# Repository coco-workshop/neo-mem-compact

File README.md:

# neo-mem-compact

> ⚠️ **UNTESTED DESIGN.** None of these boards has been built or tried in a CoCo 3.
> They have only been checked on paper: design-rule checks, an independent pin-by-pin
> check against datasheets, and simulation of the DAT board's logic. Real hardware may
> still show timing or fit problems these checks can't catch. Build them at your own
> risk, order the smallest quantity you can, and treat a first batch as prototypes.

Compact surface-mount RAM expansions for the Tandy Color Computer 3. They plug into
the CN4/CN5/CN6 expansion sockets (and, for 2 MB, the CPU socket).

| Board | What it does | Main parts |
|---|---|---|
| [**512K memory**](boards/512k) | 512K upgrade on its own | CY62146ESL 256K×16 SRAM, 74AHCT86, 2× 74x574 |
| [**2048K memory**](boards/2048k-mem) | 2 MB of RAM; runs as 512K on its own | CY62167ELL 1M×16 SRAM, 74AHCT86, 2× 74x574 |
| [**DAT**](boards/dat) | Sits under the CPU and supplies the extra address bits the 2048K memory board needs; also drives an optional turbo LED | ATF1504AS CPLD |

**Which to build:**
* **512K:** the 512K memory board. It's the cheapest option.
* **2 MB:** the 2048K memory board plus the DAT board, joined by a short bank cable
  (both headers are 2×2, laid out like the GIME-Z's bank header).
  The memory board also runs alone as 512K, so you can fit it first and add the DAT
  board later.

| 512K memory | 2048K memory | DAT |
|---|---|---|
|  |  |  |
| [layout](boards/512k/docs/preview.png) | [layout](boards/2048k-mem/docs/preview.png) | [layout](boards/dat/docs/preview.png) · [with CPU fitted](boards/dat/docs/render-cpu.png) |

*3D renders of the assembled boards, made from the real PCB layers and KiCad's
standard part models (the DAT board's wire-wrap socket is drawn as a normal socket).
The "layout" links show the flat top and bottom views.*

**Status: untested - no board has been built yet.** What *has* been checked: all
three boards pass DRC, and each finished PCB was checked independently against
datasheet pinouts (`boards/*/docs/`). The DAT board's CPLD logic passes a cycle-level
simulation in both CPU speed modes, both as written and after fitting into the chip.
Not yet confirmed on real hardware: memory timing on a real GIME (and on faster GIME
replacements), the DAT board's bank timing against /RAS, and physical fit in the case.
The DAT board's outline was fitted to an Athena-style board's layout and measured
parts heights (see [Fitting](#fitting)), not to a real machine.

## Connectors, jumpers and features

### 512K memory board
| Ref | What | Use |
|---|---|---|
| J1 | 24-pin header, **underneath** | Plugs into CN6/CN5 (the vertical socket pair left of the RAM). Pin 1 (square pad) faces the rear ports. |
| J2 | 12-pin header, **underneath** | Plugs into CN4 (the horizontal socket above the keyboard connector). Pin 1 at the left end. |

No jumpers or settings.

### 2048K memory board
| Ref | What | Use |
|---|---|---|
| J1, J2 | Same as the 512K memory board | Same fitting. |
| J3 | 2×2 header on top: a **B** row and a **G** row | Bank input from the DAT board (or any source with the same layout as the GIME-Z bank header). Pin 1 is the square pad, a B pin. |

* **J3 left open:** runs as 512K (R1/R2 hold the bank lines low).
* **2×2 cable (pin 1 to pin 1):** B to B, G to G. The two B wires can go either way
  round; swapping them only reorders memory.
* **Two single leads:** only the two B pins are needed; the motherboard provides the ground.

### DAT board
| Ref | What | Use |
|---|---|---|
| J1 | 40-pin wire-wrap socket | Sits in the CPU socket, and the 6809/6309 plugs into it. Pin 1 is the square pad, marked "CPU pin 1". |
| J2 | 2×2 header: a **B** column (board edge) and a **G** column | Bank output to memory J3. Pin 1 is the square pad, a B pin. Both B lines have 100 Ω protection (R1/R2), so a plug turned round does no harm. |
| J3 | 2×5 JTAG header | Programs the CPLD with `dat2m_top.jed`. Atmel ATDH1150USB / USB-Blaster layout (1 TCK, 2 GND, 3 TDO, 4 +5V, 5 TMS, 9 TDI, 10 GND). The CoCo must be powered on while programming. |
| J4 | 1×2 turbo LED header | Pin 1 "+" (+5V) to the LED's anode, pin 2 to its cathode. The 470 Ω resistor (R3) is on the board, so connect the LED directly. |
| JP1 | 3-pad solder jumper, **on the back** | Mode select, marked "512K JP1 2MB". |

* **JP1 as made (pads 1–2 bridged):** 2MB mode. **To force 512K:** cut the 1–2 bridge
  and bridge 2–3. Use this for old programs that write junk into the MMU registers'
  top bits.
* **Turbo LED:** lights while the CPU runs fast (`POKE 65497,0`, i.e. any write to
  `$FFD9`). It goes off with `POKE 65496,0` (`$FFD8`) or a reset.
* **Using 2MB:** after reset the machine is a normal 512K CoCo 3. Software reaches the
  extra memory by writing bits 7:6 of the MMU registers (`$FFA0`–`$FFAF`); video
  memory uses `$FF9B` bits 1:0. NitrOS-9 configured for 2MB, or a 2MB memory test,
  does this for you.

## Repository layout
| Path | Contents |
|---|---|
| `boards/<board>/hardware` | KiCad 7 project (opens in KiCad 7, 8 and 9) |
| `boards/<board>/fab` | Gerbers + drill (zip), JLCPCB BOM and placement (CPL) files |
| `boards/<board>/docs` | Schematic PDF, 3D renders, flat layout preview, DRC and verification reports (plus the DAT board's bus pin check) |
| `docs/diagrams` | The diagrams used in this README (SVG) |
| `boards/dat/cpld` | CPLD logic, testbench, fitted `dat2m_top.jed`, build script |
| `scripts/512k`, `scripts/mem`, `scripts/dat` | Each board's design definition, generators and independent checker |
| `scripts/common` | Routing, clean-up, fab-output and rendering tools shared by all boards |

## How the memory boards work
Both memory boards replace the CoCo 3's four DRAMs with one 16-bit SRAM.

* The GIME multiplexes row and column addresses onto the same pins. Two '574
  flip-flops (U3/U4) latch the row address on the falling edge of /RAS, clocked
  through one XOR gate (`RAS = ~RAS XOR 1`). That gate delay centres the sampling
  point on the row-address hold time. On the 2048K memory board the same flip-flops also
  latch the two bank bits from the DAT board.
* Flip-flops are used rather than transparent latches ('573), so the row address
  holds after /RAS rises and can't change mid-cycle even if /CAS outlasts /RAS.
* `~BHE = ~WE0 XOR 1`, `~BLE = ~WE1 XOR 1`, `~WE = ~WE1 XOR ~BHE`
  (Jim Brain's simplification). If both write lines are ever low at once (an
  invalid state), the result is "no write".
* SRAM `~CE` = `/CAS`, `~OE` = GND. The chip only responds while the column address
  is valid, so glitches on the address lines or write logic before /CAS falls are
  ignored, and page-mode accesses are safe.
* SRAM address pins, and the data pins within each byte lane, are permuted to
  simplify routing. Any consistent one-to-one mapping works.
* The 2048K memory board's R1/R2 pull the bank bits low, so with no DAT board connected it
  runs as 512K.

## How the DAT board works (2 MB)
The GIME's MMU registers are only 6 bits wide, so it can only address 512K
(64 × 8K blocks). Every CoCo 3 2 MB upgrade, from the original Disto kit onward, adds a board on the CPU bus that keeps the missing top two bits
of each MMU register and supplies them as physical address lines A20:A19.

The CPLD only listens to the CPU bus. The only signals it drives are the two bank lines
and the turbo LED.

| Register | Kept by the DAT board |
|---|---|
| `$FFA0–$FFAF` | bits 7:6 of all 16 MMU registers (the GIME keeps bits 5:0) |
| `$FF90` | bit 6 (MMU enable), bit 3 (MC3, the constant `$FExx` page) |
| `$FF91` | bit 0 (task select) |
| `$FF9B` | bits 1:0, the video bank (the Disto convention, as used by NitrOS-9) |
| `$FFD8/$FFD9` | CPU speed, used to find the CPU slot |

For each GIME memory slot it outputs either the CPU bank or the video bank:
* **CPU slots:** `mmu[task, A15:A13]` bits 7:6. It outputs bank 0 when the MMU is
  off, and for `$FExx` when MC3 is set (matching the GIME).
* **Video slots:** `$FF9B` bits 1:0.

The GIME runs memory slots at a fixed ~3.58 MHz. Counting from E's falling edge, the
fast-mode pattern is video, CPU, and the slow-mode pattern is video, idle, video,
CPU. So the CPU slot is always the one that ends when E falls: "E high" in fast
mode, "E high and Q low" in slow mode. (This matches Tony Distefano's description of
the Disto 2-Meg kit.)

All of these registers are write-only (reads come from the GIME as usual) and are
cleared by /RESET, so a reset machine is a plain 512K CoCo 3 until software writes
bits 7:6.

**Turbo LED:** J4 (+5V, cathode through R3) drives a case LED that lights whenever
the CPU runs fast: any write to `$FFD9` turns it on; `$FFD8` or /RESET turns it off.

**512K mode:** solder jumper **JP1** on the back of the DAT board selects the mode.
It ships bridged 1–2 (2 MB). Re-bridge it 2–3 to force bank 0, for any old program
that writes junk into bits 7:6 of the MMU registers.

The DAT board doesn't buffer or protect the CPU bus. It only listens: every CPLD pin
on the CPU bus is an input, the four clock and control lines (E, Q, R/W, /RESET) use
input-only pins that can't drive at all, and the bus safety check (see
[The CPLD](#the-cpld-boardsdatcpld)) rejects any build that would make a bus pin an
output. Its two bank outputs pass through 100 Ω resistors (R1/R2), so a cable plugged
in backwards can't short them.

## Fitting
1. **Memory board (either size):** remove the four DRAMs (IC16–IC19) and cut C65 and
   C66. On a PAL machine they're left of the GIME; on an NTSC machine they're nearer
   the DRAM sockets. J1 goes into CN6/CN5 (the vertical socket pair left of the
   DRAM), with pin 1 (square pad) toward the rear ports. J2 goes into CN4 (the
   horizontal socket above the keyboard connector), with pin 1 at the left end.
2. **DAT board (2 MB only):** the CPU must be socketed. Pull the 6809/6309, plug the
   DAT board into the CPU socket with pin 1 (square pad, marked "CPU pin 1")
   matching the socket's pin 1, then plug the CPU into the DAT board. The board is
   30.1 × 65.5 mm and sits about 5 mm up, on top of the CPU socket:
   * Over the socket it is the CPU's width, with a slim tab (8.5 mm wide) on the
     pin-1 side holding the turbo LED (J4), bank (J2) and JTAG (J3) headers. The tab
     starts about halfway along the socket, clear of the tall caps near the pin-1
     end (C2, C56).
   * The CPLD end reaches 16 mm past the CPU's pin-20 end and is 3.8 mm wider on
     the pin-21 side. On the Athena layout it stays clear of the parts around it:
     about 3.7 mm to C4, 7.2 mm to a OneROM in the ROM socket, 7.9 mm to C55.
   * Anything under the board taller than the socket (5 mm) must be moved or laid
     flat, for example a capacitor added just past the CPU's pin-20 end.
3. Link DAT **J2** to memory **J3** with a short 2×2 female–female cable wired pin 1
   to pin 1. Both headers have a **B** pair and a **G** pair (marked on the
   silkscreen; pin 1 = square pad = B): match B to B and G to G. Which B goes to
   which doesn't matter - swapping the two bank lines only reorders memory. Two
   single leads on the B pins alone also work (the grounds are extra). See the
   [bank cable diagram](docs/diagrams/bank-cable.svg).

## The CPLD (`boards/dat/cpld`)
* `dat2m.v` holds the logic and `dat2m_tb.v` is its testbench
  (`iverilog dat2m.v dat2m_tb.v && vvp a.out`).
* `dat2m_top.v` is the top level. It's generated from the PCB, so its `//PIN:` list
  matches the copper exactly.
* **`dat2m_top.jed` is ready to program** (`dat2m_top.fit` is the fitter report).
  It was built with [hoglet67/atf15xx_yosys](https://github.com/hoglet67/atf15xx_yosys)
  (Yosys plus Atmel's `fit1504` from ProChip 5.0.x, run under Wine). With every pin
  locked to the PCB it fits in 50 of 64 macrocells, with E on the global clock
  (pin 37), /RESET on global clear (pin 39) and the turbo LED on pin 14. The
  fitter's gate-level output passes the same 129-check testbench as the source.
* To rebuild: `ATF15XX=/path/to/atf15xx_yosys boards/dat/cpld/build.sh`. It
  synthesises, fits, and re-runs the testbench on the fitted netlist.
* **Bus safety check:** `scripts/dat/check_pins.py` reads the fitter report
  (`dat2m_top.fit`) and the PCB and fails unless BANK0, BANK1 and the turbo LED are the only outputs,
  every CPLD pin wired to the CPU socket is an input, and the pins the fitter
  left unused are unconnected. `build.sh` runs it after every fit; the result for
  the committed `.jed` is in `boards/dat/docs/pin-check.txt`.
* In `dat2m_top.v` the E and Q inputs are called `ECLK`/`QCLK`: top-level ports named
  `E` or `Q` clash with cell pin names, and `fit1504` then rejects the netlist.
* Program `dat2m_top.jed` through J3 (10-pin, Atmel ATDH1150USB / USB-Blaster layout)
  with Microchip ATMISP (included with ProChip). Or convert it to SVF and play it
  with OpenOCD or UrJTAG from any compatible adapter. Power the CoCo while
  programming.

## Ordering (JLCPCB)
**These are untested prototypes** (see the warning at the top): order the minimum
quantity, and expect that a first build may need fixes.

Each board has its own Gerbers, BOM and CPL file in `boards/<board>/fab/`. Upload the
gerbers zip (2 layers, 1.6 mm), then the BOM and CPL for assembly. Check part
rotations in JLC's placement preview: each chip's pin-1 dot should sit on its
silkscreen triangle. Ordering all boards together shares shipping.

**Parts (both memory boards):**
| Ref | Part | LCSC | Alternatives |
|---|---|---|---|
| U2 | TI SN74AHCT86PWR | C471866 | Nexperia 74AHCT86PW (C554719), or any 5 V TTL-input '86 in TSSOP-14 (AHCT, VHCT, ACT). Not HCT: too slow for the /RAS clock path. |
| U3, U4 | Toshiba 74VHCT574AFT(BE) | C7421311 | Nexperia 74AHCT574PW (C282328), Toshiba 74VHCT574AFT (C2677834), any ACT574 in TSSOP-20; HCT574 as a last resort (slower, less margin) |
| U1 (512K) | CY62146ESL-45ZSXIT (reel) | C2953196 | CY62146ESL-45ZSXI (the same chip on a tray, e.g. from DigiKey or Mouser), or the dearer CY62146ELL. Not the CY62146EV30 (3 V only). |
| U1 (2048K) | CY62167ELL-45ZXI | C2950509 | Not the CY62167EV30 (3 V only). |

**Never** use HC (CMOS-level inputs), LV or LVC (3.3 V) logic.

**DAT board:**
* **U1:** ATF1504AS-10AU44. LCSC (C219301) is usually out of stock and expensive;
  DigiKey, Mouser and RS stock it for about $5. Untick U1 in JLC's BOM, let JLC fit
  the 0402 capacitors and resistors, and hand-solder the CPLD (TQFP-44, 0.8 mm pitch).
* **R1, R2** 100 Ω (C25076) and **R3** 470 Ω (C25117), all JLC basic parts.
* **J1** is a 40-pin **wire-wrap** DIP socket (long square tails, e.g. Mill-Max
  123-43-640-41-001000), mounted on top with its tails pushed through the board and
  trimmed to about 6 mm, so they plug into the CoCo's CPU socket. The holes are
  1.0 mm for the 0.64 mm square tails.

**Hand-solder** all through-hole parts: memory board headers J1/J2 on the
**bottom** (J3, 2×2, on top, 2048K memory board only), and the DAT board's J1, J2 (2×2),
J3 (2×5, JTAG) and J4 (1×2, turbo LED).

## First power-up
1. Check for shorts between +5V and GND on every board.
2. Fit the memory board alone and run a full 512K memory test (e.g. under NitrOS-9,
   or a RAM test program). On the 2048K memory board leave J3 open (bank 0).
3. If you have a scope, check /WE0 and /WE1 against /CAS at the end of a write. The
   design assumes /CAS rises before, or together with, the write line.
4. **2 MB:** program the CPLD, fit the DAT board, and check the machine boots as a
   512K CoCo 3. Then check BANK0/BANK1 at memory J3 settle **before** /RAS falls (it's
   latched there), in both fast and slow mode. The design expects /RAS to fall at
   least ~15 ns after the E/Q edge that starts the slot. Probe E and Q on the CPU's
   own pins, the bank lines on the DAT board's J2 B pins, and GND/+5V on its JTAG header.
5. Test 2 MB with NitrOS-9 configured for 2 MB, or a 2 MB memory test.

## Regenerating
Each board is defined in `scripts/<board>/design.py` (`512k`, `mem`, `dat`). Needs
KiCad 7's Python bindings (`pcbnew`), `shapely`, `scipy`, Java 21 and
[Freerouting](https://github.com/freerouting/freerouting) 2.x. For example, the
2048K memory board:
```sh
B=boards/2048k-mem/hardware/neo-mem-2048k-mem
python3 scripts/mem/make_sch.py && python3 scripts/mem/make_pcb.py      # unrouted board
FREEROUTING_JAR=/path/freerouting-2.1.0.jar FR_EXTRA=--router.optimizer.max_passes=40 \
  python3 scripts/common/route.py $B.kicad_pcb /tmp/r.kicad_pcb 60
python3 scripts/common/finish.py /tmp/r.kicad_pcb /tmp/drc.txt          # strip stubs, DRC
python3 scripts/common/schnets.py /tmp/r.kicad_pcb $B.kicad_pro
cp /tmp/r.kicad_pcb $B.kicad_pcb
python3 scripts/mem/verify.py $B.kicad_pcb $B.kicad_sch
python3 scripts/common/fab.py boards/2048k-mem/hardware neo-mem-2048k-mem \
  boards/2048k-mem/fab boards/2048k-mem/docs scripts/mem/bom.json
```
The 512K memory and DAT boards work the same way (the DAT checker also takes
`boards/dat/cpld/dat2m_top.v`, and `finish.py` takes `JP1` as a keepout). The memory
boards' fine pitches need the 0.15 mm default clearance set in their `.kicad_pro`
(the DAT board uses 0.2 mm). Autorouting
isn't deterministic; the committed boards are the ones that were checked.

The 3D renders (`boards/*/docs/render*.png`) come from
`python3 scripts/common/render_all.py`, which also needs `rsvg-convert`, `pyvista`
and `cadquery-ocp`. It downloads KiCad's STEP part models into `~/.cache/kicad-3d`
the first time. The diagrams in `docs/diagrams` are hand-drawn SVGs, except
`dat-timing.svg`, which `python3 scripts/common/diagram_timing.py` generates.

## License and credit
Derived from **cc3-512k** by Ciaran Anscomb (<https://gitlab.com/sixxie/cc3-512k>):
the traced CN4/CN5/CN6 pinout, connector positions, outline envelope and design
approach, with the XOR logic from Jim Brain (RETRO Innovations). The DAT approach
follows Tony Distefano's published description of the Disto 2-Meg kit. Released,
like the original, under the
[Creative Commons Attribution-ShareAlike 4.0 International](LICENSE) license.

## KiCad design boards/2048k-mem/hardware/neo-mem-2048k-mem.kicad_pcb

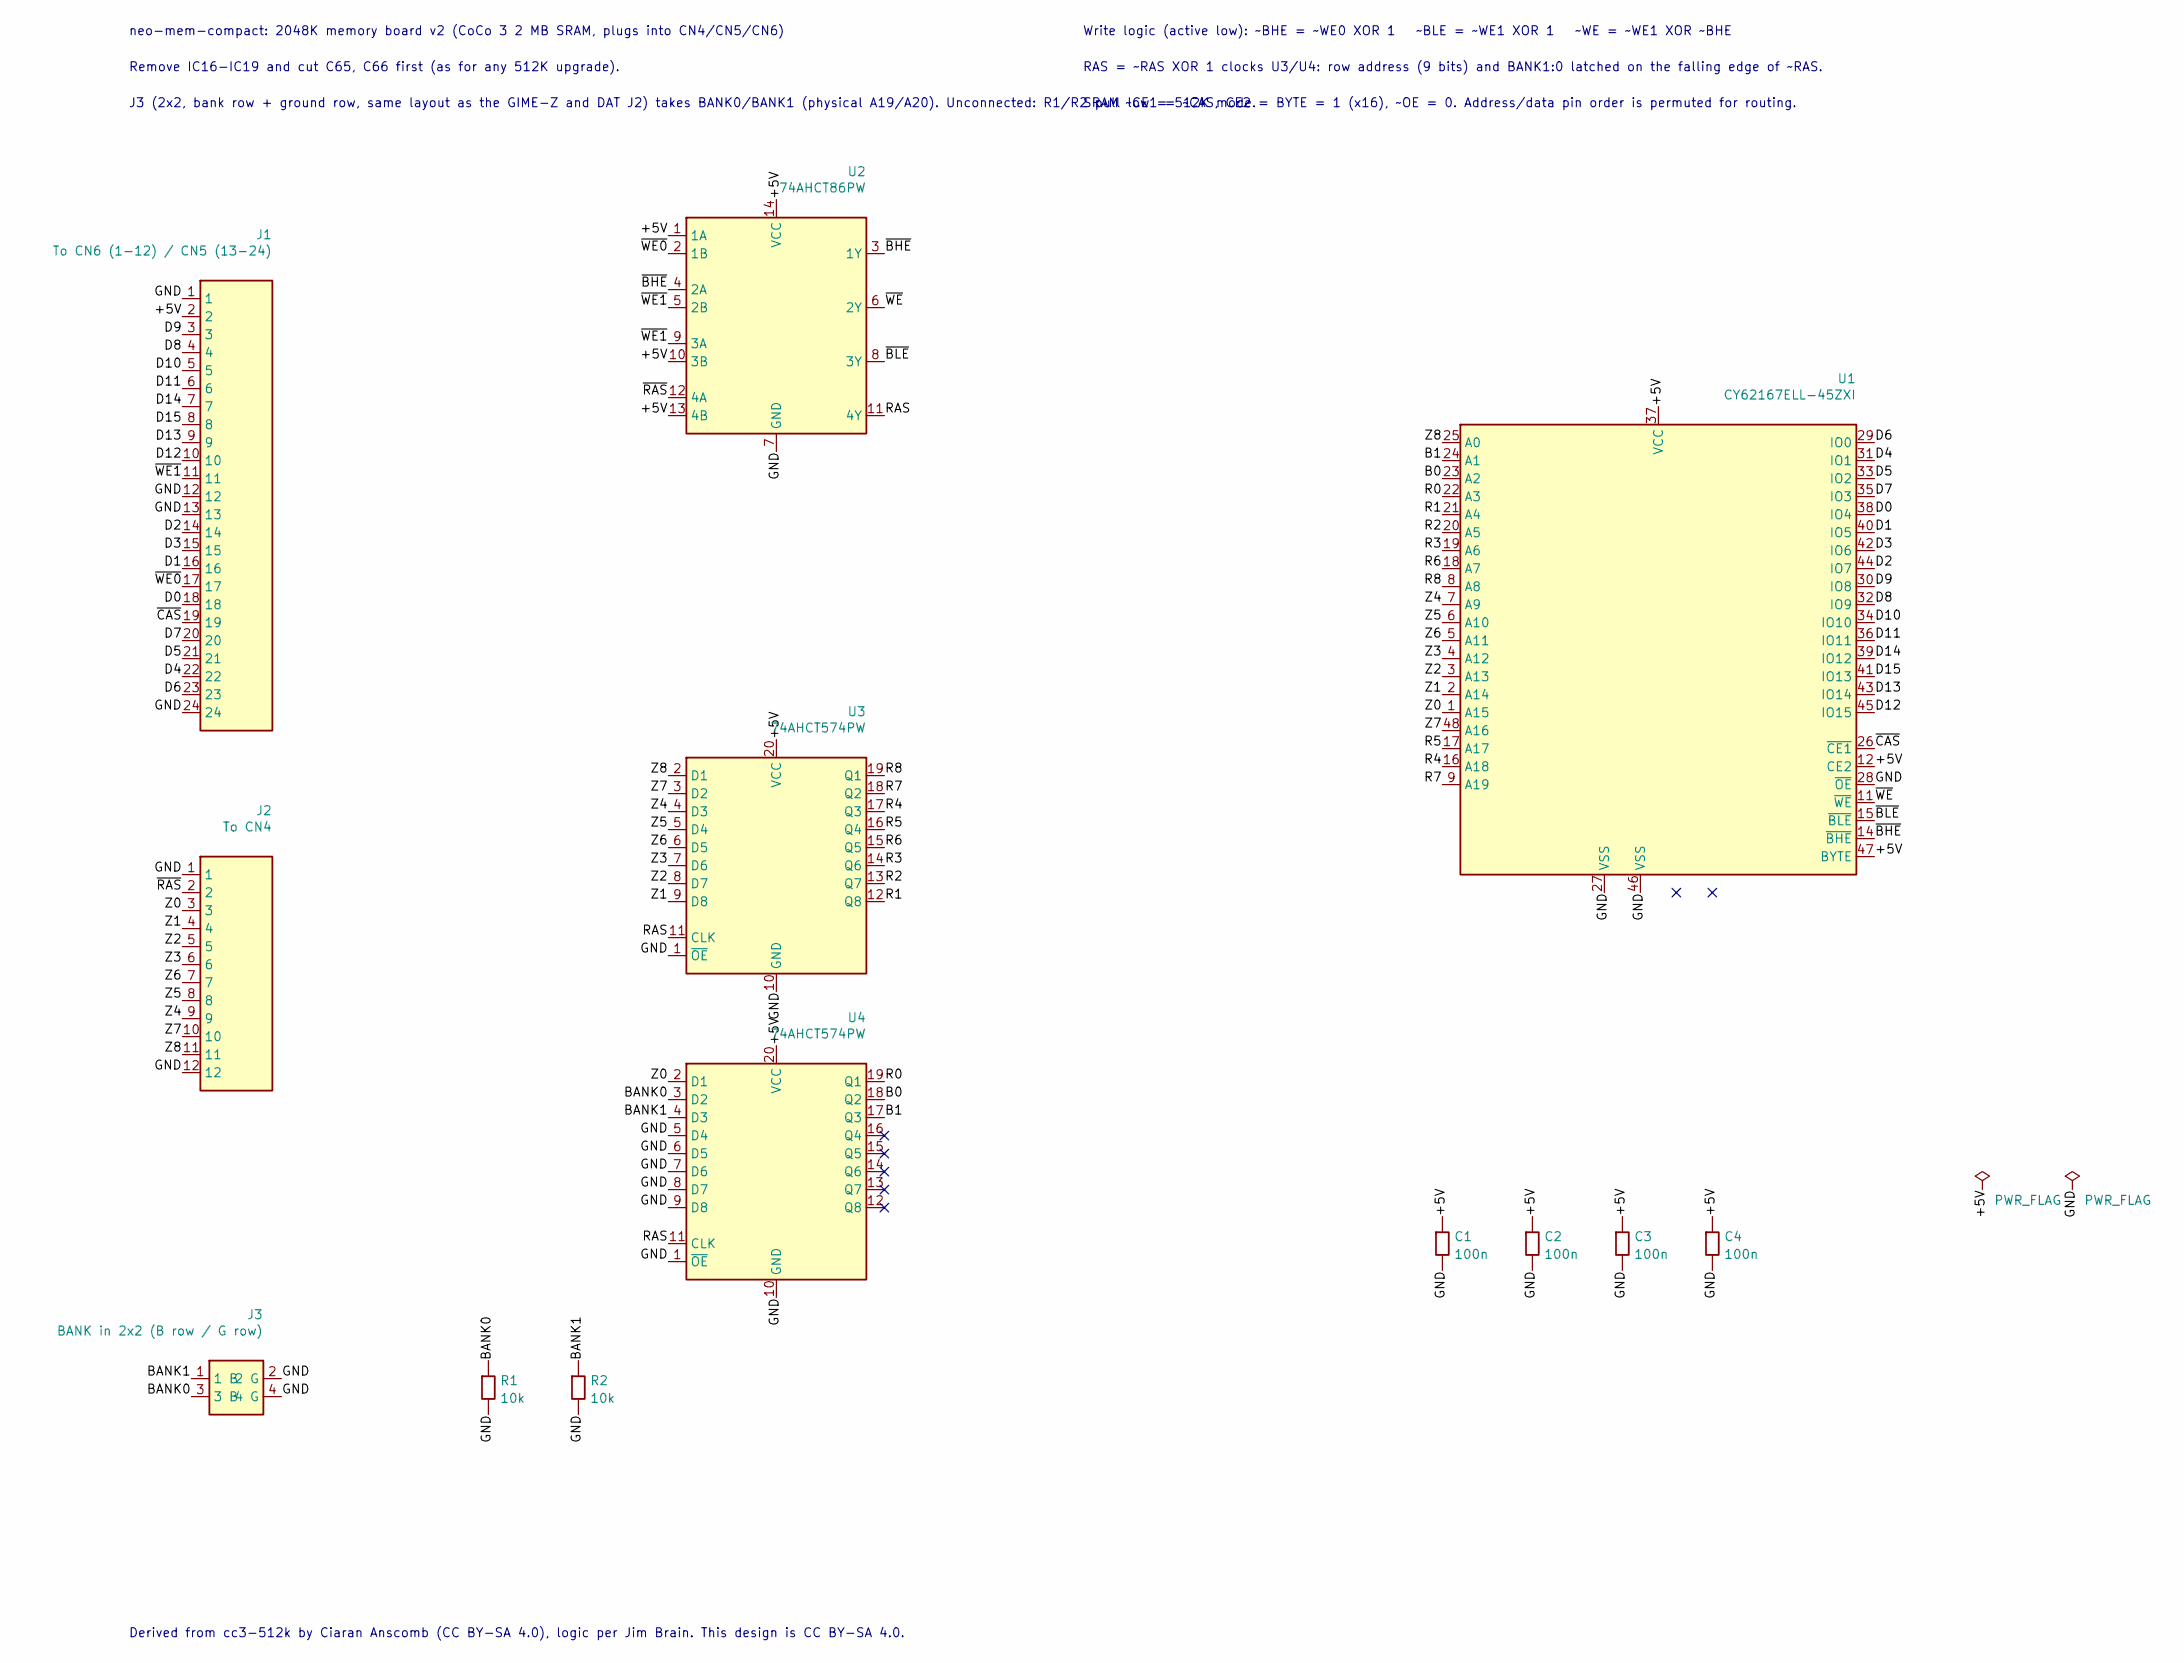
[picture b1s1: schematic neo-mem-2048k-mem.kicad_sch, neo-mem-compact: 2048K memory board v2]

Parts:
C1, C2, C3, C4: 100n; C_0402_1005Metric
J1: To CN6 (1-12) / CN5 (13-24); PinHeader_1x24_P2.54mm_Vertical
J2: To CN4; PinHeader_1x12_P2.54mm_Vertical
J3: BANK in 2x2 (B row / G row); PinHeader_2x02_P2.54mm_Vertical
R1, R2: 10k; R_0402_1005Metric
U1: CY62167ELL-45ZXI; TSOP-I-48_18.4x12mm_P0.5mm
U2: 74AHCT86PW; TSSOP-14_4.4x5mm_P0.65mm
U3, U4: 74AHCT574PW; TSSOP-20_4.4x6.5mm_P0.65mm

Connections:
/+5V: C1.1, C2.1, C3.1, C4.1, J1.2, U1.12 (CE2), U1.37 (VCC), U1.47 (BYTE), U2.1 (1A), U2.10 (3B), U2.13 (4B), U2.14 (VCC), U3.20 (VCC), U4.20 (VCC)
/B0: U1.23 (A2), U4.18 (Q2)
/B1: U1.24 (A1), U4.17 (Q3)
/BANK0: J3.3 (3 B), R1.1, U4.3 (D2)
/BANK1: J3.1 (1 B), R2.1, U4.4 (D3)
/D0: J1.18, U1.38 (IO4)
/D1: J1.16, U1.40 (IO5)
/D2: J1.14, U1.44 (IO7)
/D3: J1.15, U1.42 (IO6)
/D4: J1.22, U1.31 (IO1)
/D5: J1.21, U1.33 (IO2)
/D6: J1.23, U1.29 (IO0)
/D7: J1.20, U1.35 (IO3)
/D8: J1.4, U1.32 (IO9)
/D9: J1.3, U1.30 (IO8)
/D10: J1.5, U1.34 (IO10)
/D11: J1.6, U1.36 (IO11)
/D12: J1.10, U1.45 (IO15)
/D13: J1.9, U1.43 (IO14)
/D14: J1.7, U1.39 (IO12)
/D15: J1.8, U1.41 (IO13)
/GND: C1.2, C2.2, C3.2, C4.2, J1.1, J1.12, J1.13, J1.24, J2.1, J2.12, J3.2 (2 G), J3.4 (4 G), R1.2, R2.2, U1.27 (VSS), U1.28 (~OE), U1.46 (VSS), U2.7 (GND), U3.1 (~OE), U3.10 (GND), U4.1 (~OE), U4.5 (D4), U4.6 (D5), U4.7 (D6), U4.8 (D7), U4.9 (D8), U4.10 (GND)
/R0: U1.22 (A3), U4.19 (Q1)
/R1: U1.21 (A4), U3.12 (Q8)
/R2: U1.20 (A5), U3.13 (Q7)
/R3: U1.19 (A6), U3.14 (Q6)
/R4: U1.16 (A18), U3.17 (Q3)
/R5: U1.17 (A17), U3.16 (Q4)
/R6: U1.18 (A7), U3.15 (Q5)
/R7: U1.9 (A19), U3.18 (Q2)
/R8: U1.8 (A8), U3.19 (Q1)
/RAS: U2.11 (4Y), U3.11 (CLK), U4.11 (CLK)
/Z0: J2.3, U1.1 (A15), U4.2 (D1)
/Z1: J2.4, U1.2 (A14), U3.9 (D8)
/Z2: J2.5, U1.3 (A13), U3.8 (D7)
/Z3: J2.6, U1.4 (A12), U3.7 (D6)
/Z4: J2.9, U1.7 (A9), U3.4 (D3)
/Z5: J2.8, U1.6 (A10), U3.5 (D4)
/Z6: J2.7, U1.5 (A11), U3.6 (D5)
/Z7: J2.10, U1.48 (A16), U3.3 (D2)
/Z8: J2.11, U1.25 (A0), U3.2 (D1)
/~BHE: U1.14 (~BHE), U2.3 (1Y), U2.4 (2A)
/~BLE: U1.15 (~BLE), U2.8 (3Y)
/~CAS: J1.19, U1.26 (~CE1)
/~RAS: J2.2, U2.12 (4A)
/~WE0: J1.17, U2.2 (1B)
/~WE1: J1.11, U2.5 (2B), U2.9 (3A)
/~WE: U1.11 (~WE), U2.6 (2Y)

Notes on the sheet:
neo-mem-compact: 2048K memory board v2 (CoCo 3 2 MB SRAM, plugs into CN4/CN5/CN6)
Remove IC16-IC19 and cut C65, C66 first (as for any 512K upgrade).
J3 (2x2, bank row + ground row, same layout as the GIME-Z and DAT J2) takes BANK0/BANK1 (physical A19/A20). Unconnected: R1/R2 pull low = 512K mode.
Write logic (active low): ~BHE = ~WE0 XOR 1 ~BLE = ~WE1 XOR 1 ~WE = ~WE1 XOR ~BHE
RAS = ~RAS XOR 1 clocks U3/U4: row address (9 bits) and BANK1:0 latched on the falling edge of ~RAS.
SRAM ~CE1 = ~CAS, CE2 = BYTE = 1 (x16), ~OE = 0. Address/data pin order is permuted for routing.
Derived from cc3-512k by Ciaran Anscomb (CC BY-SA 4.0), logic per Jim Brain. This design is CC BY-SA 4.0.

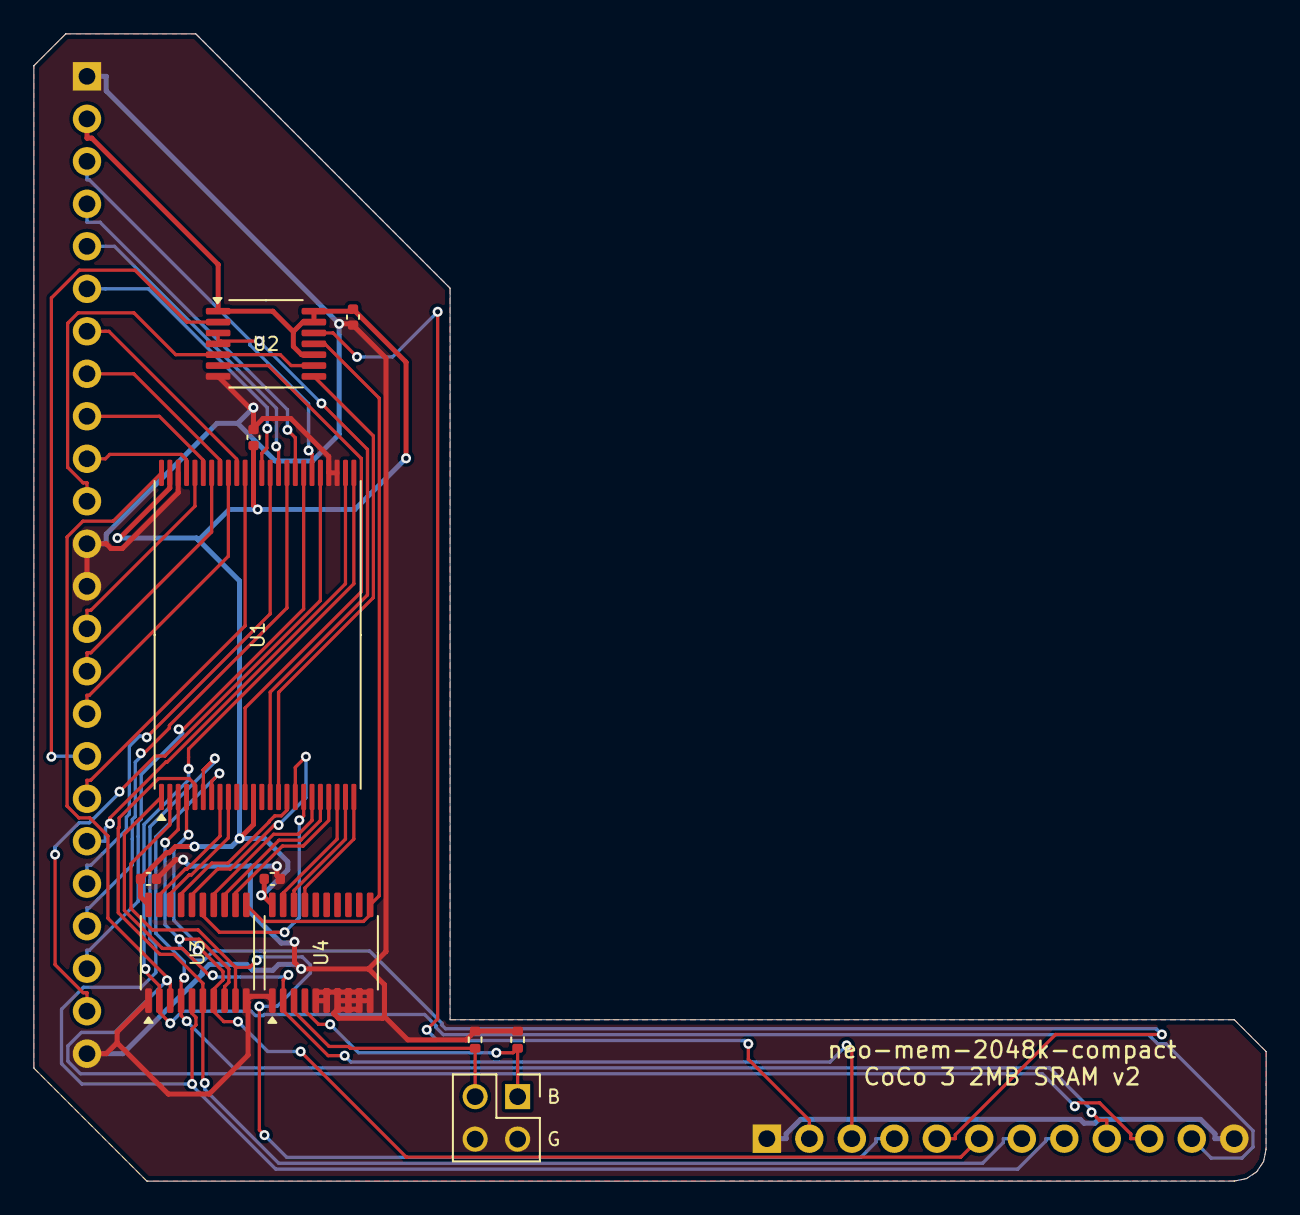
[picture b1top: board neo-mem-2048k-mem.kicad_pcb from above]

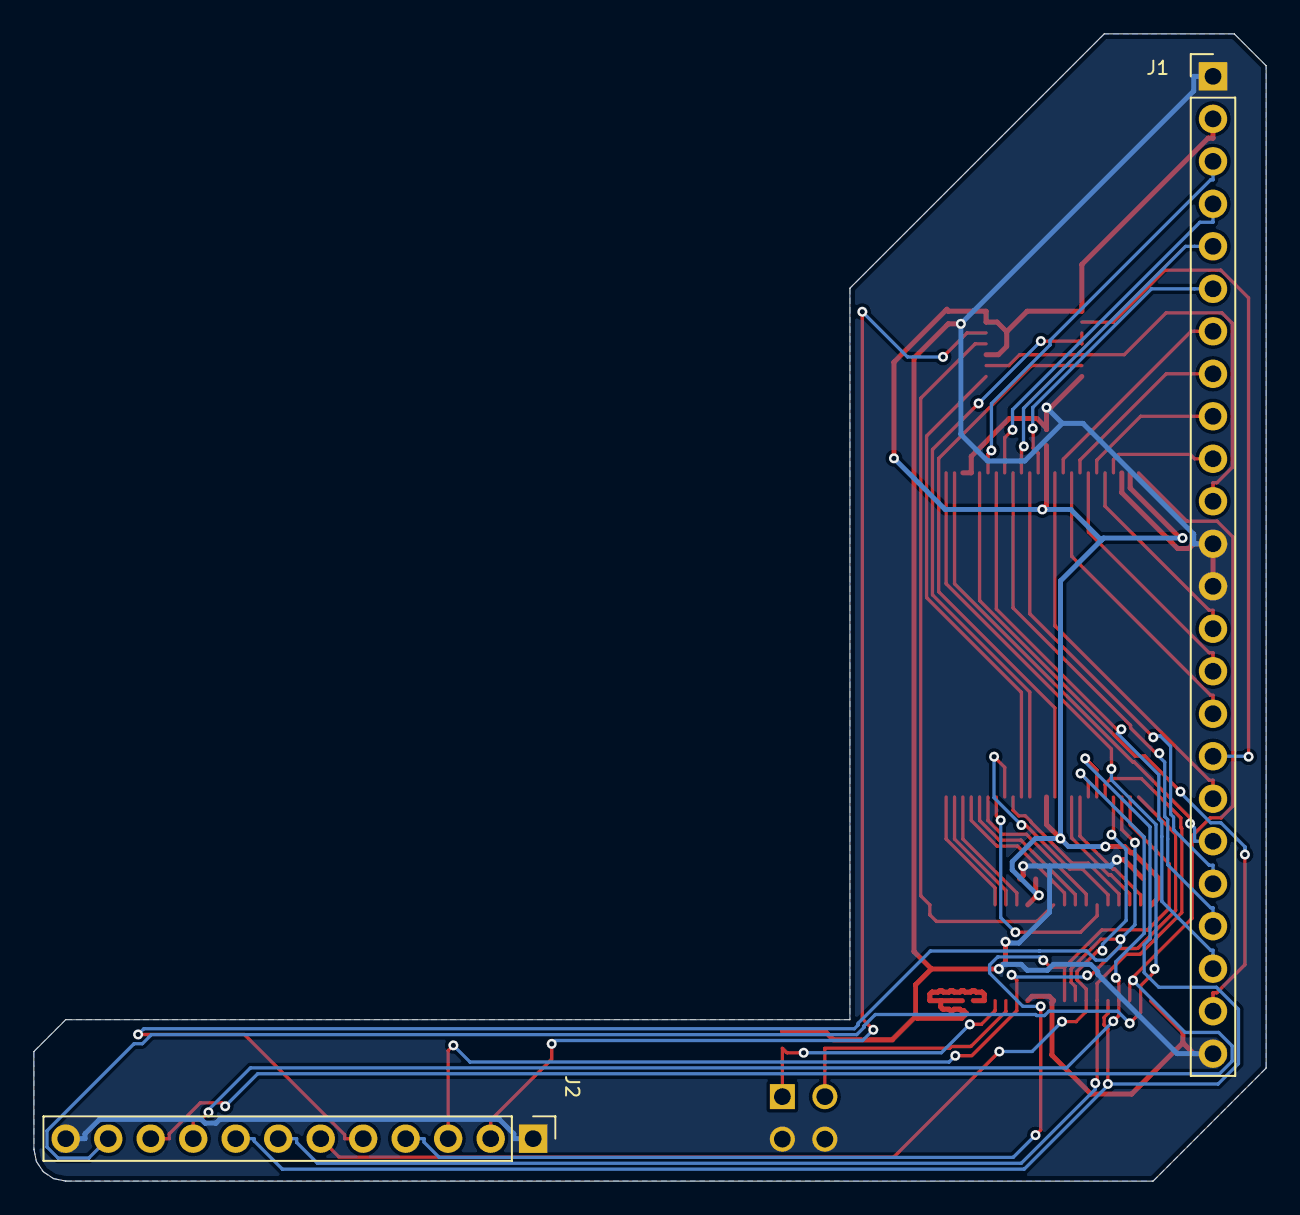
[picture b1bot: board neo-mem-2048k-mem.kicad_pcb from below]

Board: 2 copper layers, 73.7 x 68.6 mm, 13 parts (2 on the bottom side), 48 nets.

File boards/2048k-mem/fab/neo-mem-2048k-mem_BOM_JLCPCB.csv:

Comment,Designator,Footprint,LCSC Part #
CY62167ELL-45ZXI 1Mx16 SRAM (5V),U1,TSOP-I-48_18.4x12mm_P0.5mm,C2950509
SN74AHCT86PWR quad XOR (alt: 74AHCT86PW C554719),U2,TSSOP-14_4.4x5mm_P0.65mm,C471866
74VHCT574AFT(BE) octal D flip-flop (alt: 74AHCT574PW C282328),"U3,U4",TSSOP-20_4.4x6.5mm_P0.65mm,C7421311
100nF 16V X7R 0402,"C1,C2,C3,C4",C_0402_1005Metric,C1525
10k 1% 0402,"R1,R2",R_0402_1005Metric,C25744

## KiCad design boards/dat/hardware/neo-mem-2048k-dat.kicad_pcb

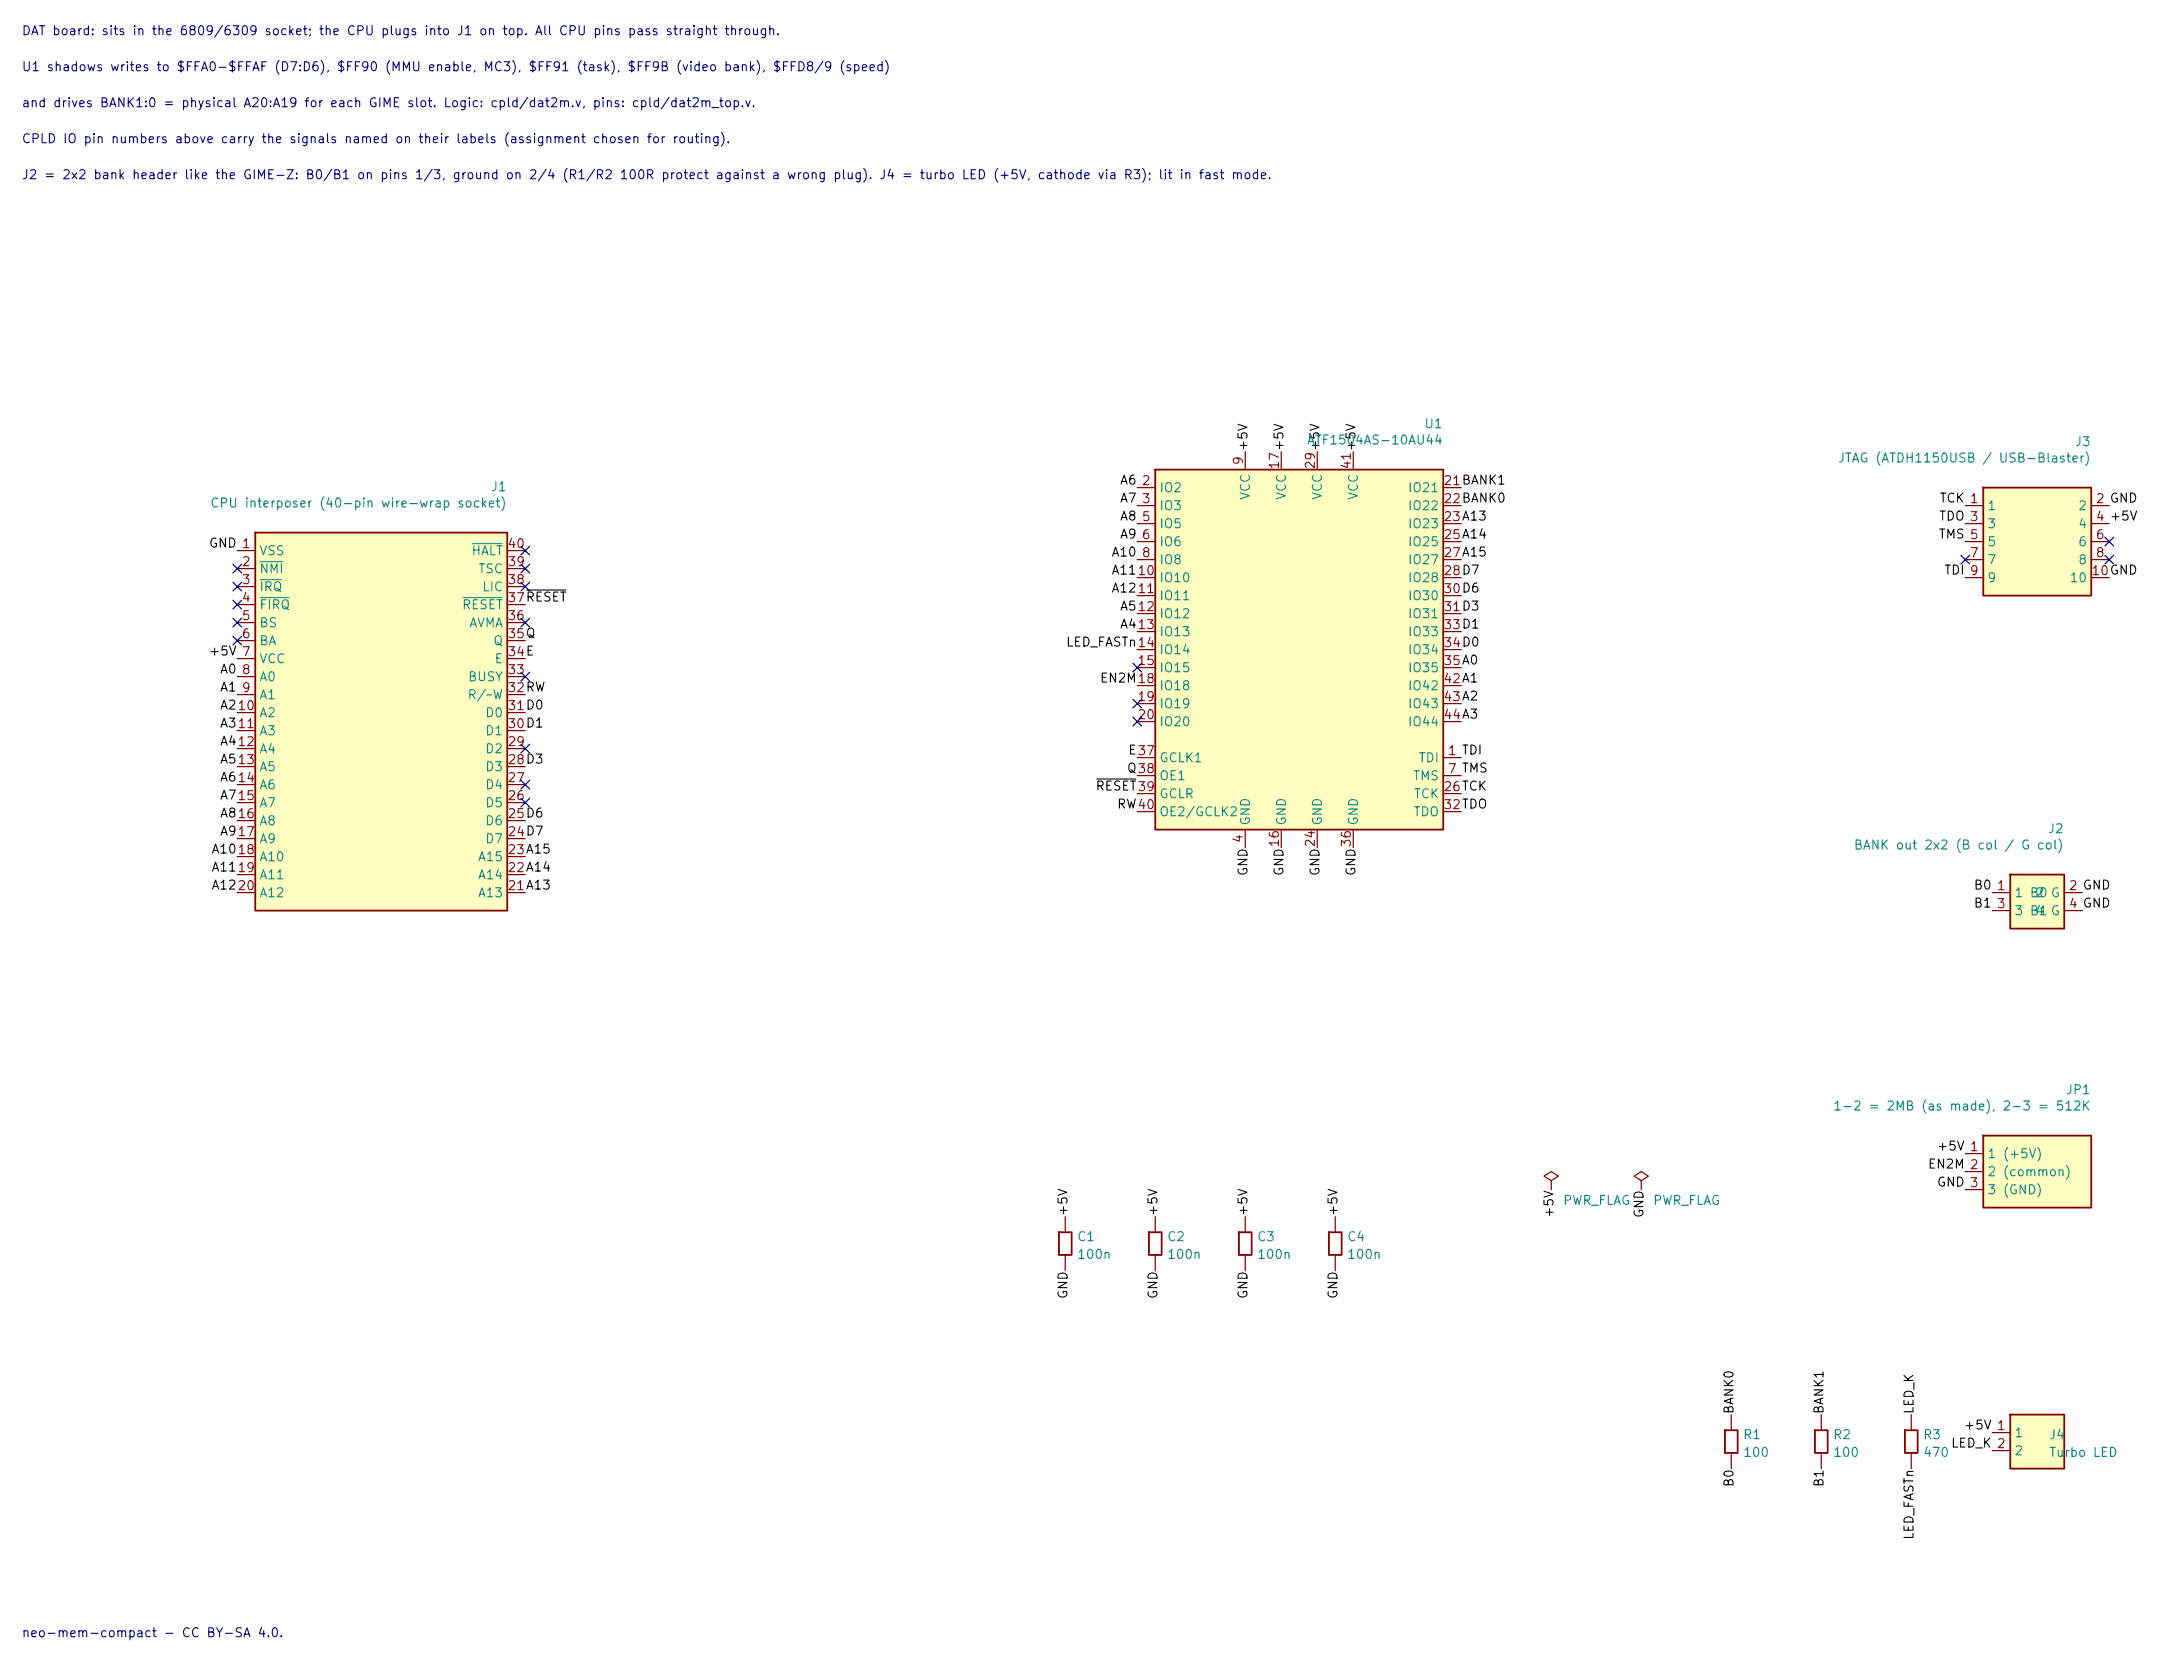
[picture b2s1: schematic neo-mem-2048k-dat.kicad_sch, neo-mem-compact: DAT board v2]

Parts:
C1, C2, C3, C4: 100n; C_0402_1005Metric
J1: CPU interposer (40-pin wire-wrap socket); DIP-40_W15.24mm
J2: BANK out 2x2 (B col / G col); PinHeader_2x02_P2.54mm_Vertical
J3: JTAG (ATDH1150USB / USB-Blaster); PinHeader_2x05_P2.54mm_Vertical
J4: Turbo LED; PinHeader_1x02_P2.54mm_Vertical
JP1: 1-2 = 2MB (as made), 2-3 = 512K; SolderJumper-3_P1.3mm_Bridged12_RoundedPad1.0x1.5mm
R1, R2: 100; R_0402_1005Metric
R3: 470; R_0402_1005Metric
U1: ATF1504AS-10AU44; TQFP-44_10x10mm_P0.8mm

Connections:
/+5V: C1.1, C2.1, C3.1, C4.1, J1.7 (VCC), J3.4, J4.1, JP1.1 (1 (+5V)), U1.9 (VCC), U1.17 (VCC), U1.29 (VCC), U1.41 (VCC)
/A0: J1.8 (A0), U1.35 (IO35)
/A1: J1.9 (A1), U1.42 (IO42)
/A2: J1.10 (A2), U1.43 (IO43)
/A3: J1.11 (A3), U1.44 (IO44)
/A4: J1.12 (A4), U1.13 (IO13)
/A5: J1.13 (A5), U1.12 (IO12)
/A6: J1.14 (A6), U1.2 (IO2)
/A7: J1.15 (A7), U1.3 (IO3)
/A8: J1.16 (A8), U1.5 (IO5)
/A9: J1.17 (A9), U1.6 (IO6)
/A10: J1.18 (A10), U1.8 (IO8)
/A11: J1.19 (A11), U1.10 (IO10)
/A12: J1.20 (A12), U1.11 (IO11)
/A13: J1.21 (A13), U1.23 (IO23)
/A14: J1.22 (A14), U1.25 (IO25)
/A15: J1.23 (A15), U1.27 (IO27)
/B0: J2.1 (1 B0), R1.2
/B1: J2.3 (3 B1), R2.2
/BANK0: R1.1, U1.22 (IO22)
/BANK1: R2.1, U1.21 (IO21)
/D0: J1.31 (D0), U1.34 (IO34)
/D1: J1.30 (D1), U1.33 (IO33)
/D3: J1.28 (D3), U1.31 (IO31)
/D6: J1.25 (D6), U1.30 (IO30)
/D7: J1.24 (D7), U1.28 (IO28)
/E: J1.34 (E), U1.37 (GCLK1)
/EN2M: JP1.2 (2 (common)), U1.18 (IO18)
/GND: C1.2, C2.2, C3.2, C4.2, J1.1 (VSS), J2.2 (2 G), J2.4 (4 G), J3.2, J3.10, JP1.3 (3 (GND)), U1.4 (GND), U1.16 (GND), U1.24 (GND), U1.36 (GND)
/LED_FASTn: R3.2, U1.14 (IO14)
/LED_K: J4.2, R3.1
/Q: J1.35 (Q), U1.38 (OE1)
/RW: J1.32 (R/~W), U1.40 (OE2/GCLK2)
/TCK: J3.1, U1.26 (TCK)
/TDI: J3.9, U1.1 (TDI)
/TDO: J3.3, U1.32 (TDO)
/TMS: J3.5, U1.7 (TMS)
/~RESET: J1.37 (~RESET), U1.39 (GCLR)

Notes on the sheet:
DAT board: sits in the 6809/6309 socket; the CPU plugs into J1 on top. All CPU pins pass straight through.
U1 shadows writes to $FFA0-$FFAF (D7:D6), $FF90 (MMU enable, MC3), $FF91 (task), $FF9B (video bank), $FFD8/9 (speed)
and drives BANK1:0 = physical A20:A19 for each GIME slot. Logic: cpld/dat2m.v, pins: cpld/dat2m_top.v.
CPLD IO pin numbers above carry the signals named on their labels (assignment chosen for routing).
J2 = 2x2 bank header like the GIME-Z: B0/B1 on pins 1/3, ground on 2/4 (R1/R2 100R protect against a wrong plug). J4 = turbo LED (+5V, cathode via R3); lit in fast mode.
neo-mem-compact - CC BY-SA 4.0.

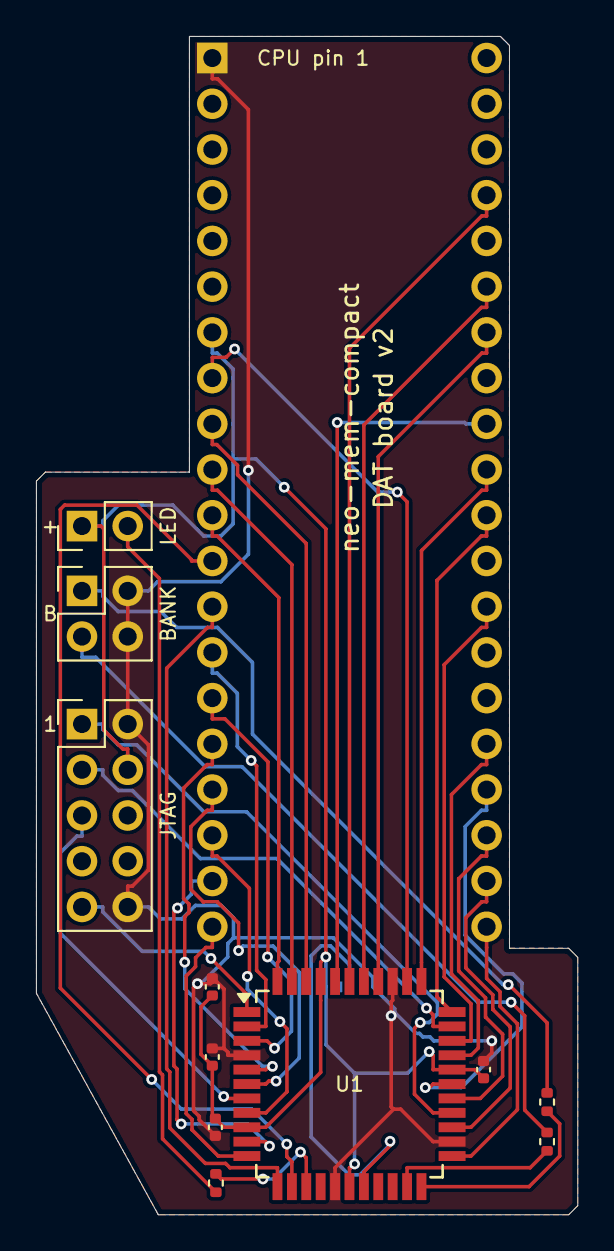
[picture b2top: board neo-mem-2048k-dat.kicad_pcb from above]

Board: 2 copper layers, 30.1 x 65.5 mm, 13 parts (1 on the bottom side), 38 nets.

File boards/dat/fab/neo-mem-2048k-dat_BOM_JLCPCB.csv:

Comment,Designator,Footprint,LCSC Part #
"ATF1504AS-10AU44 CPLD (64 macrocells, 5V)",U1,TQFP-44_10x10mm_P0.8mm,C219301
100nF 16V X7R 0402,"C1,C2,C3,C4",C_0402_1005Metric,C1525
100R 1% 0402,"R1,R2",R_0402_1005Metric,C25076
470R 1% 0402,R3,R_0402_1005Metric,C25117
